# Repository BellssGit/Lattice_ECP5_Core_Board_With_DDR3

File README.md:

# Lattice_ECP5_Core_Board_With_DDR3
A 6 layer Board, Using Lattice LFE5U-25F-BGA256 FPGA with 32bit wide DDR3 memory.

Connectivity:
  
  1. 8 Channel LVDS working up to 800Mbps per channel
  2. 24bit RGB display or general IO
  3. FT232H with FT245 FIFO support

On Board memory:
  
  1. 128Mbit Flash
  2. 2x2Gbit 16x2bit wide DDR3 memory

A [blog post](https://www.emoe.xyz/lattice_ecp5_board/) about this board (Chinese Only)

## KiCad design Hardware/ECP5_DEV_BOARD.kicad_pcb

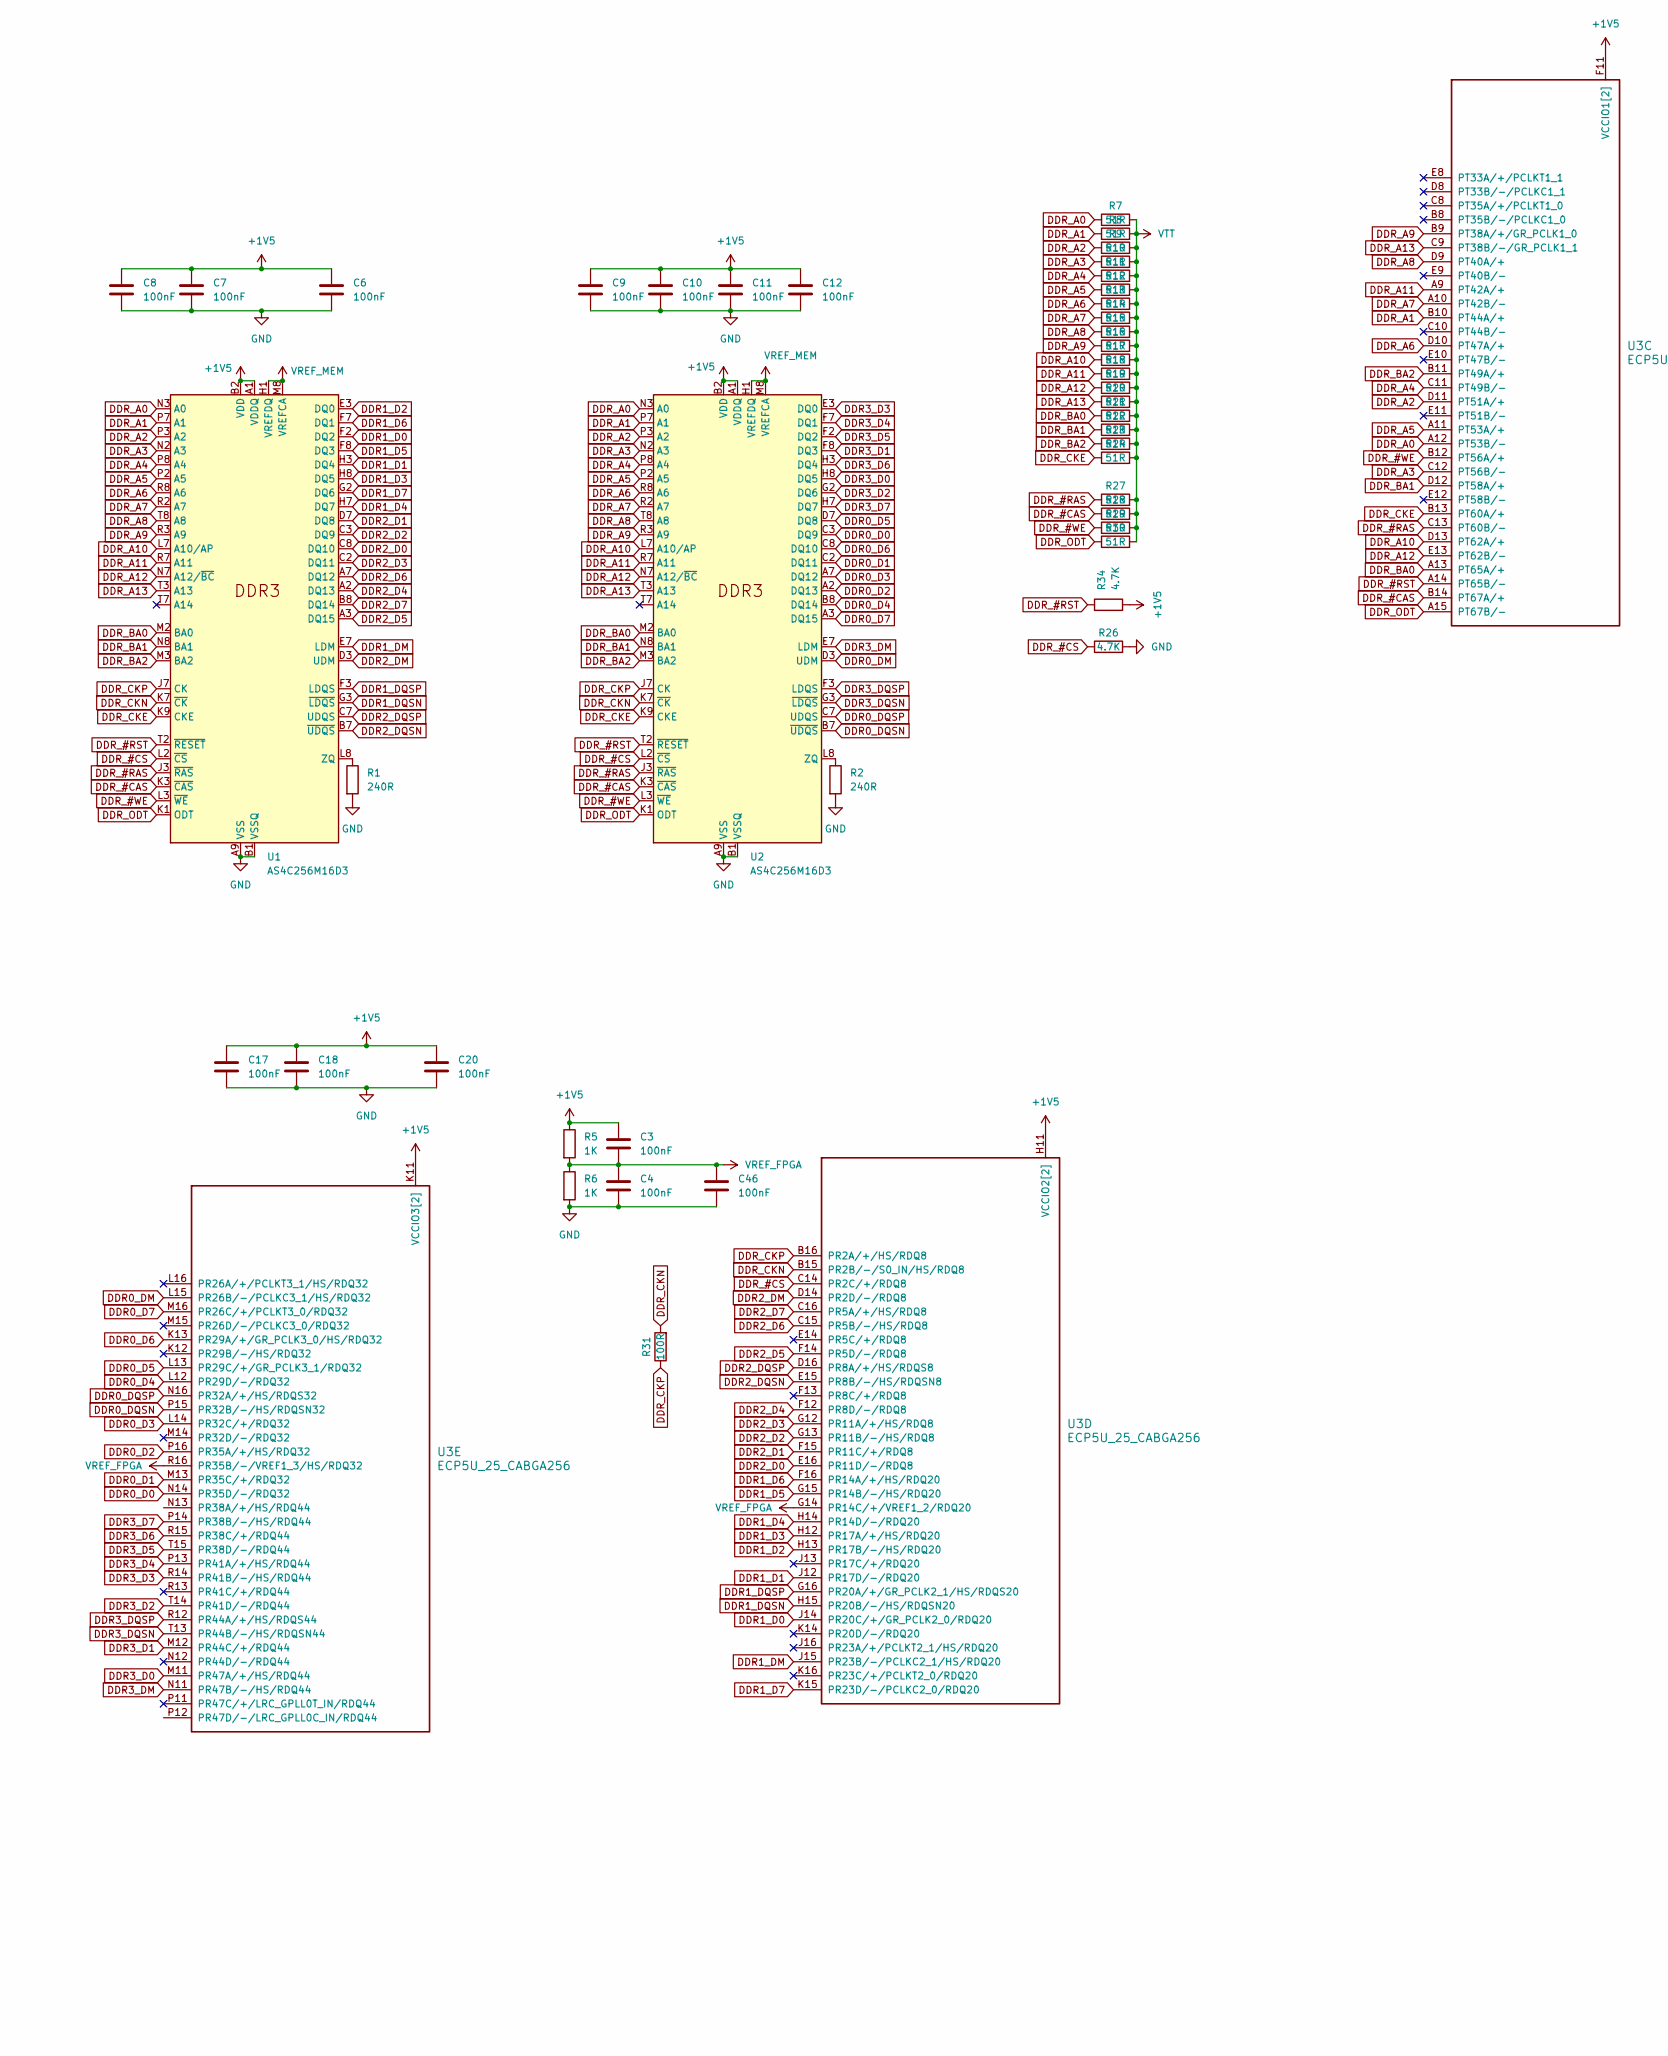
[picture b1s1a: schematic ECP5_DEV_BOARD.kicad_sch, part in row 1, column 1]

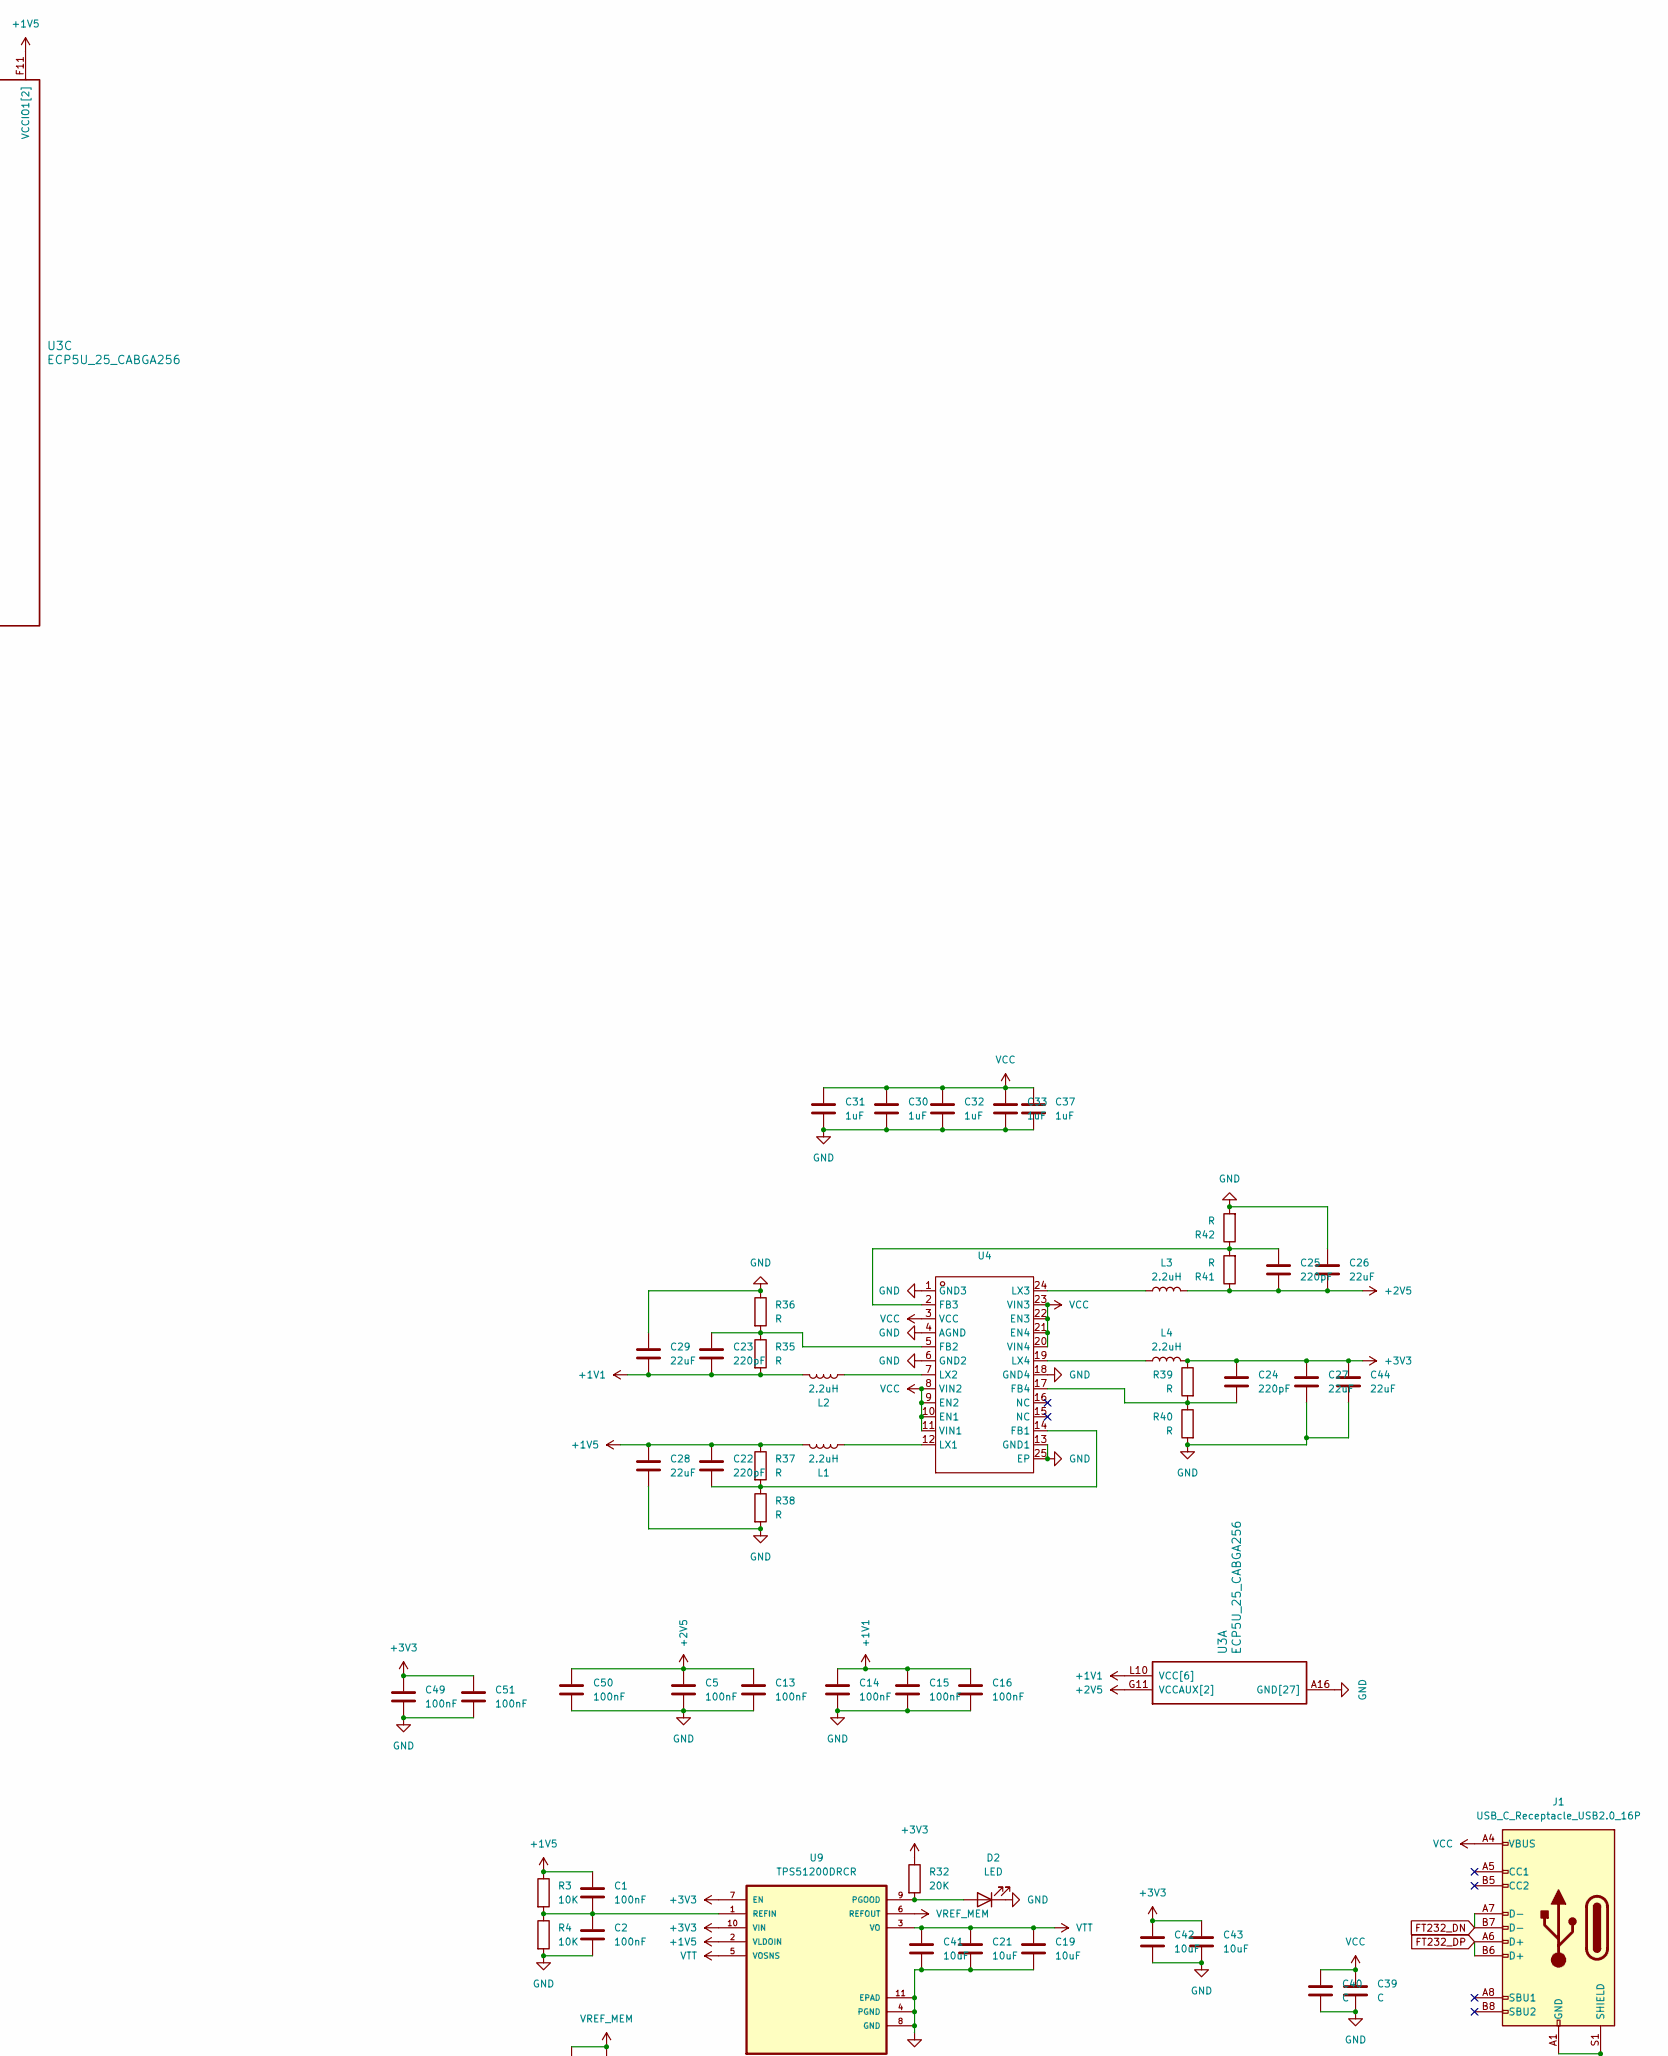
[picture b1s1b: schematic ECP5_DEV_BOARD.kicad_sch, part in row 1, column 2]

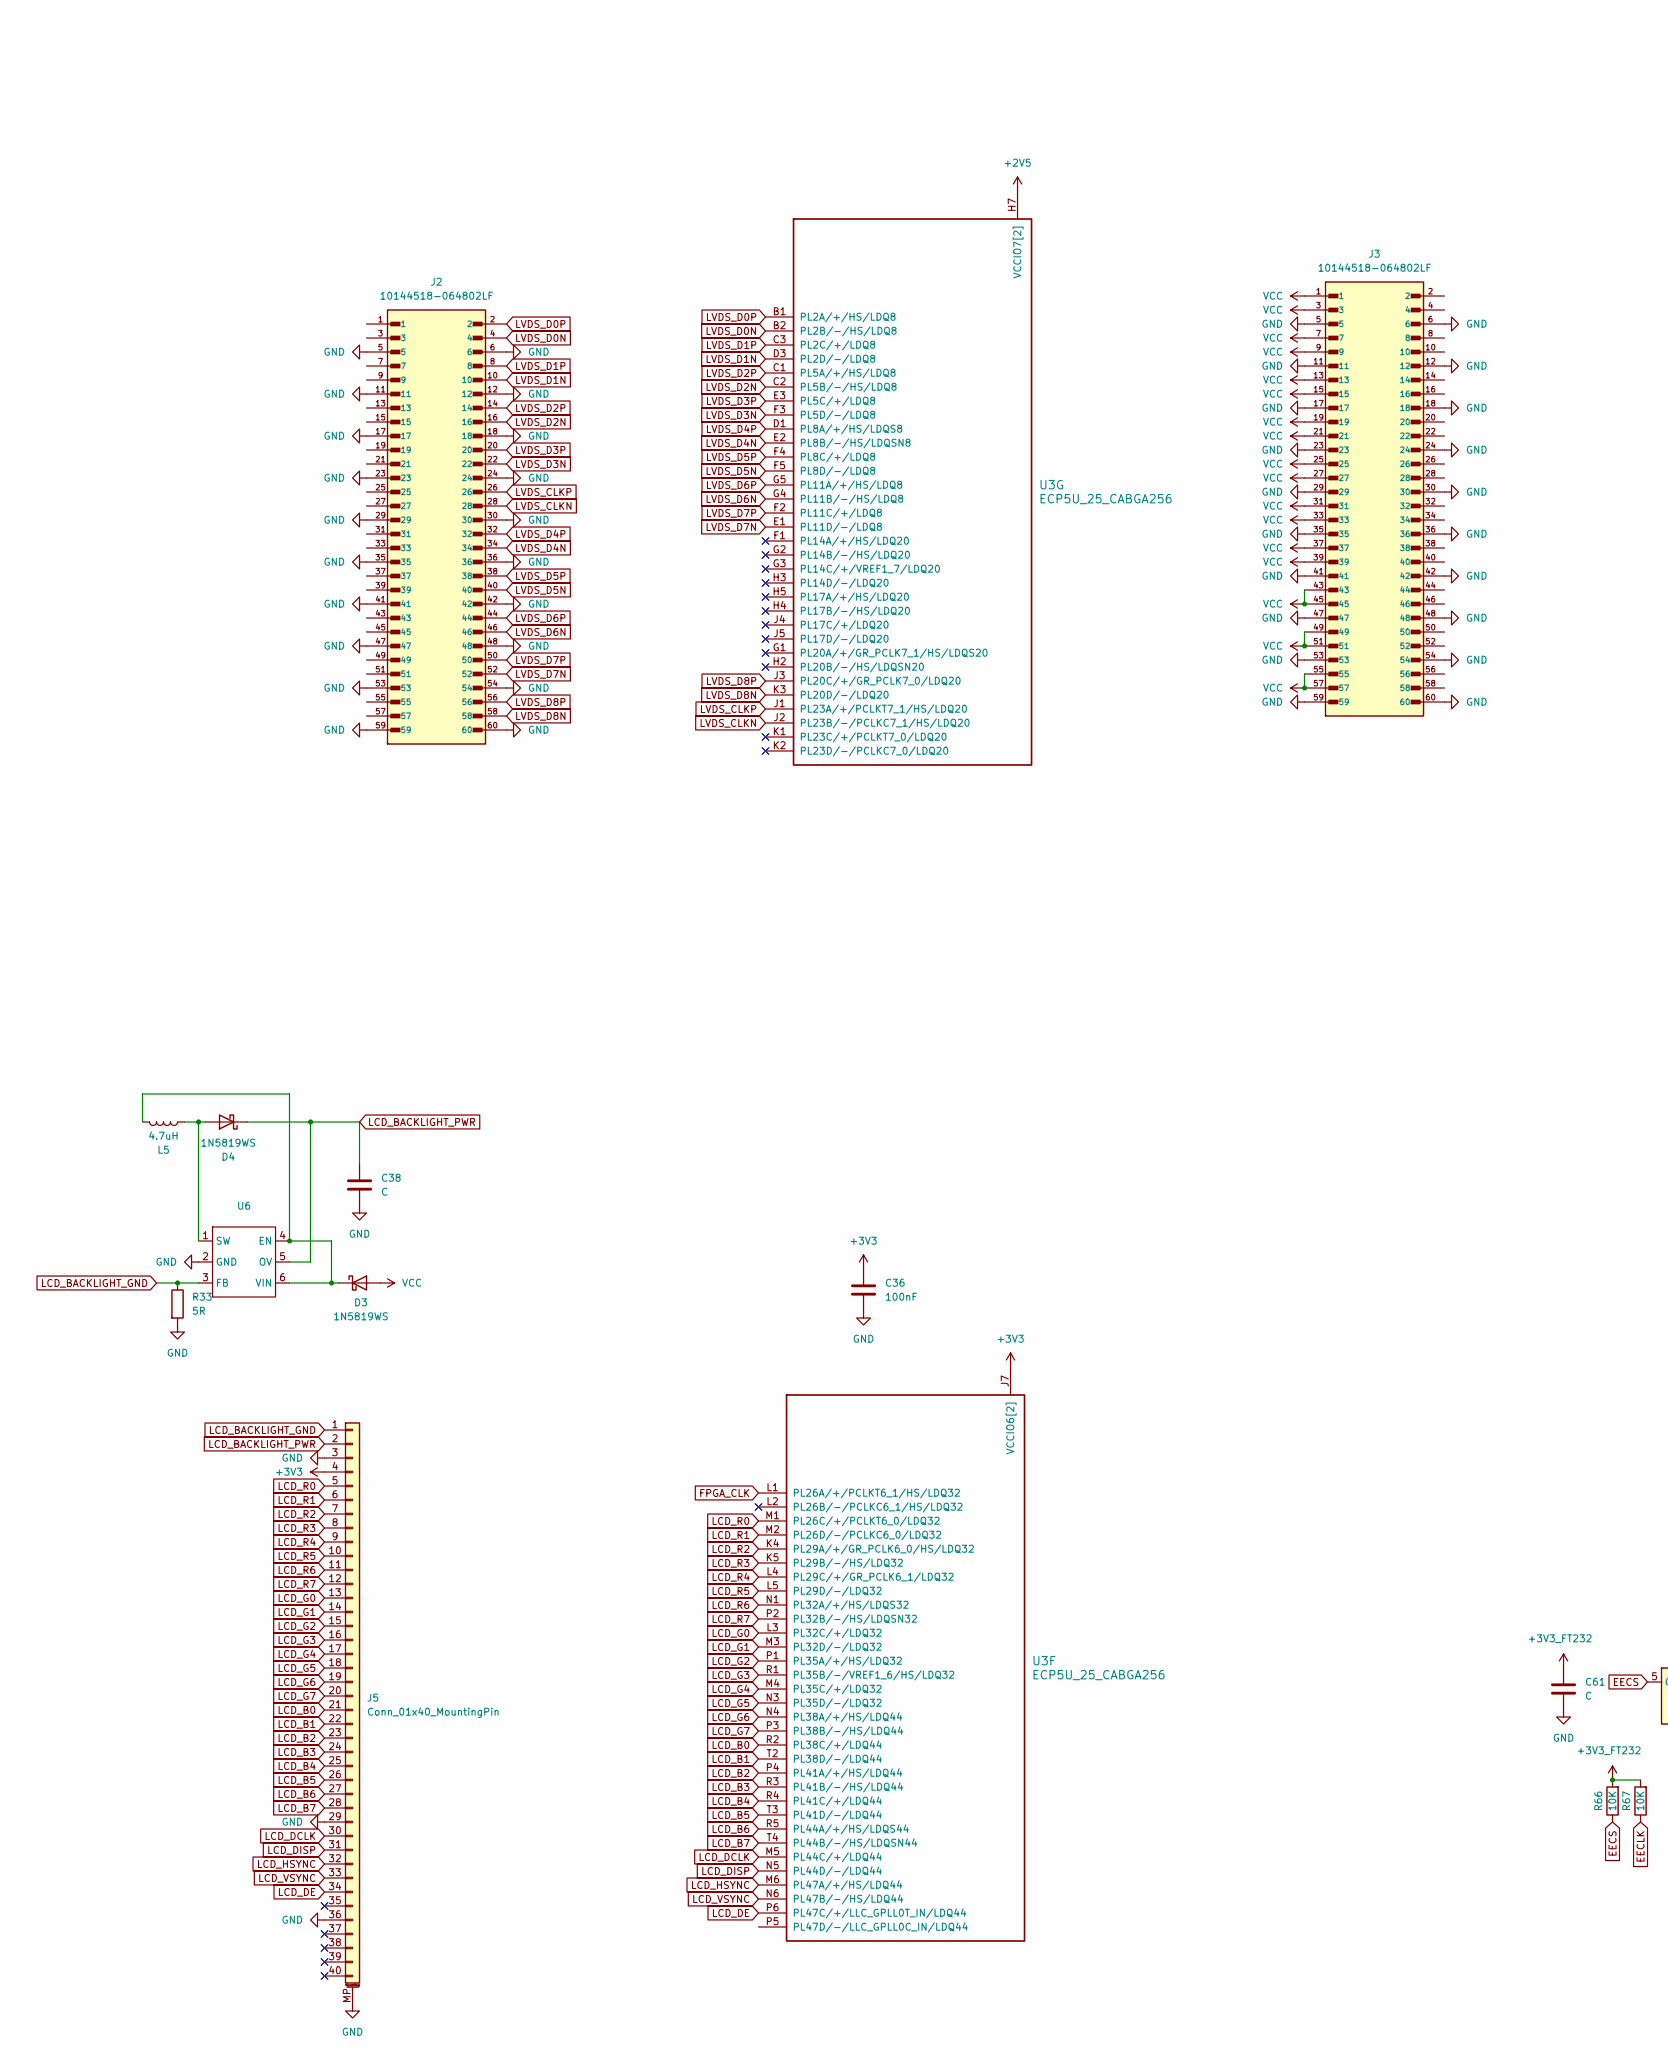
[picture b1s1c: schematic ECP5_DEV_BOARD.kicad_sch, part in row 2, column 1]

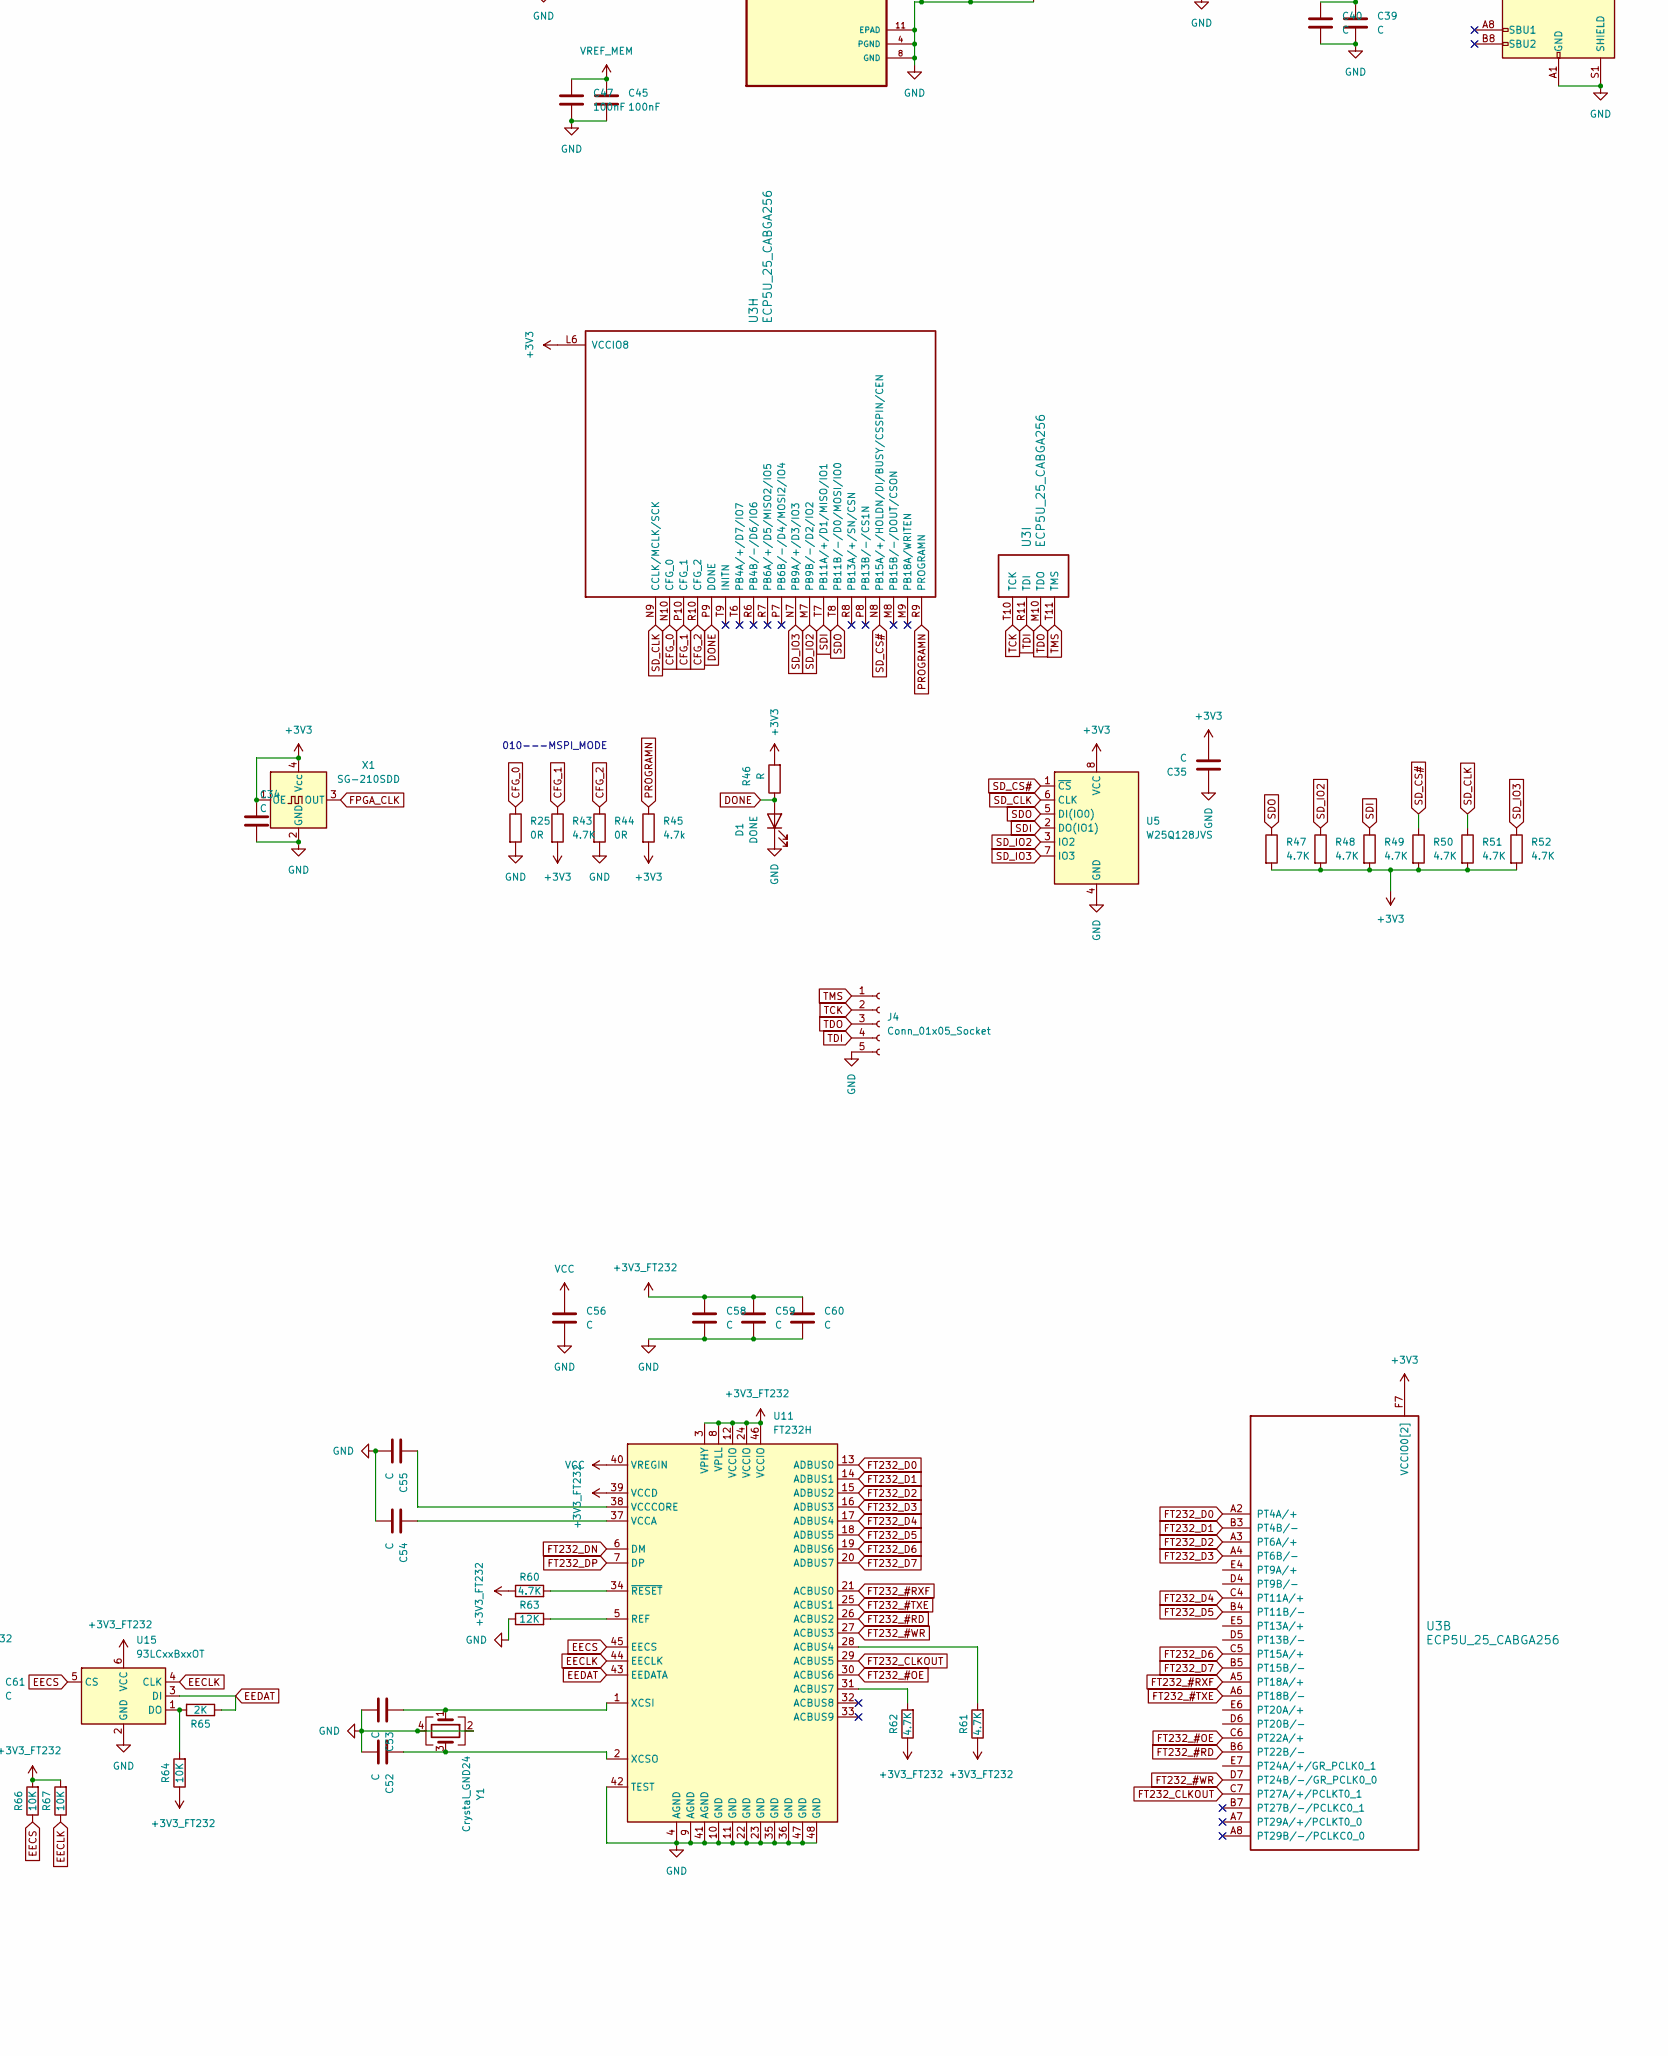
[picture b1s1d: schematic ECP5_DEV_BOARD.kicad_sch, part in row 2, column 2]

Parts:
C1, C2, C3, C4, C47: 100nF; C_0603_1608Metric
C5, C6, C7, C8, C9, C10, C11, C12, C13, C14, C15, C16, C17, C18, C20, C36, C45, C46, C49, C50, C51: 100nF; C_0402_1005Metric
C19, C21, C41, C42, C43: 10uF; C_0603_1608Metric
C22, C23, C24, C25: 220pF; C_0603_1608Metric
C26, C27, C28, C29, C44: 22uF; C_0805_2012Metric
C30, C31, C32, C33, C37: 1uF; C_0603_1608Metric
C34, C35, C52, C53, C54, C55, C56, C58, C59, C60, C61: C; C_0603_1608Metric
C38, C39, C40: C; C_0805_2012Metric
D1: DONE; LED_0603_1608Metric_Pad1.05x0.95mm_HandSolder
D2: LED; LED_0603_1608Metric
D3, D4: 1N5819WS; D_SOD-323
J1: USB_C_Receptacle_USB2.0_16P; USB_C_Receptacle_G-Switch_GT-USB-7010ASV
J2, J3: 10144518-064802LF; AMPHENOL_10144518-064802LF; PARTREV H
J4: Conn_01x05_Socket; PinSocket_1x05_P2.54mm_Vertical
J5: Conn_01x40_MountingPin; TE_4-1734839-0_1x40-1MP_P0.5mm_Horizontal
L1, L2, L3, L4: 2.2uH; L_Changjiang_FNR252010S
L5: 4.7uH; L_Changjiang_FNR252010S
R1, R2: 240R; R_0402_1005Metric
R3, R4, R64, R66, R67: 10K; R_0603_1608Metric
R5, R6: 1K; R_0603_1608Metric
R7, R8, R9, R10, R11, R12, R13, R14, R15, R16, R17, R18, R19, R20, R21, R22, R23, R24, R27, R28, R29, R30: 51R; R_0402_1005Metric
R25, R44: 0R; R_0402_1005Metric
R26, R34, R43: 4.7K; R_0402_1005Metric
R31: 100R; R_0402_1005Metric
R32: 20K; R_0603_1608Metric
R33: 5R; R_0603_1608Metric
R35, R36, R37, R38, R39, R40, R41, R42: R; R_0603_1608Metric
R45: 4.7k; R_0402_1005Metric
R46: R; R_0603_1608Metric_Pad0.98x0.95mm_HandSolder
R47, R48, R49, R50, R51, R52: 4.7K; R_0603_1608Metric_Pad0.98x0.95mm_HandSolder
R60, R61, R62: 4.7K; R_0603_1608Metric
R63: 12K; R_0603_1608Metric
R65: 2K; R_0603_1608Metric
U1, U2: AS4C256M16D3; BGA-96_9.0x13.0mm_Layout2x3x16_P0.8mm
U3: ECP5U_25_CABGA256; BGA-256_14.0x14.0mm_Layout16x16_P0.8mm_Ball0.45mm_Pad0.32mm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
U4: VQFN-24-1EP_4x4mm_P0.5mm_EP2.5x2.5mm
U5: W25Q128JVS; SOIC-8_5.23x5.23mm_P1.27mm
U6: SOT-23-6
U9: TPS51200DRCR; VREG_V62_16624-01YE
U11: FT232H; LQFP-48_7x7mm_P0.5mm
U15: 93LCxxBxxOT; SOT-23-6
X1: SG-210SDD; Oscillator_SMD_Abracon_ASE-4Pin_3.2x2.5mm
Y1: Crystal_GND24; Crystal_SMD_3225-4Pin_3.2x2.5mm

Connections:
+1V1: C14.1, C15.1, C16.1, C23.2, C29.2, L2.1, R35.2, U3.G6 (VCC[6]), U3.G7 (VCC[6]), U3.G9 (VCC[6]), U3.L8 (VCC[6]), U3.L9 (VCC[6]), U3.L10 (VCC[6])
+1V5: C1.1, C3.1, C6.1, C7.1, C8.1, C9.1, C10.1, C11.1, C12.1, C17.1, C18.1, C20.1, C22.1, C28.1, L1.1, R3.1, R5.1, R34.2, R37.1, U1.A1 (VDDQ), U1.A8 (VDDQ), U1.B2 (VDD), U1.C1 (VDDQ), U1.C9 (VDDQ), U1.D2 (VDDQ), U1.D9 (VDD), U1.E9 (VDDQ), U1.F1 (VDDQ), U1.G7 (VDD), U1.H2 (VDDQ), U1.H9 (VDDQ), U1.K2 (VDD), U1.K8 (VDD), U1.N1 (VDD), U1.N9 (VDD), U1.R1 (VDD), U1.R9 (VDD), U2.A1 (VDDQ), U2.A8 (VDDQ), U2.B2 (VDD), U2.C1 (VDDQ), U2.C9 (VDDQ), U2.D2 (VDDQ), U2.D9 (VDD), U2.E9 (VDDQ), U2.F1 (VDDQ), U2.G7 (VDD), U2.H2 (VDDQ), U2.H9 (VDDQ), U2.K2 (VDD), U2.K8 (VDD), U2.N1 (VDD), U2.N9 (VDD), U2.R1 (VDD), U2.R9 (VDD), U3.F10 (VCCIO1[2]), U3.F11 (VCCIO1[2]), U3.H11 (VCCIO2[2]), U3.J11 (VCCIO2[2]), U3.K11 (VCCIO3[2]), U3.L11 (VCCIO3[2]), U9.2 (VLDOIN)
+2V5: C5.1, C13.1, C25.1, C26.2, C50.1, L3.2, R41.1, U3.G11 (VCCAUX[2]), U3.H6 (VCCIO7[2]), U3.H7 (VCCIO7[2]), U3.L7 (VCCAUX[2])
+3V3: C24.1, C27.1, C34.1, C35.2, C36.1, C42.1, C43.1, C44.1, C49.1, C51.1, J5.4, L4.2, R32.1, R39.1, R43.2, R45.2, R46.2, R47.2, R48.2, R49.2, R50.2, R51.2, R52.2, U3.F6 (VCCIO0[2]), U3.F7 (VCCIO0[2]), U3.J6 (VCCIO6[2]), U3.J7 (VCCIO6[2]), U3.L6 (VCCIO8), U5.8 (VCC), U9.7 (EN), U9.10 (VIN), X1.1 (OE), X1.4 (Vcc)
+3V3_FT232: C58.1, C59.1, C60.1, C61.1, R60.1, R61.1, R62.1, R64.1, R66.2, R67.2, U11.3 (VPHY), U11.8 (VPLL), U11.12 (VCCIO), U11.24 (VCCIO), U11.39 (VCCD), U11.46 (VCCIO), U15.6 (VCC)
CFG_0: R25.1, U3.N10 (CFG_0)
CFG_1: R43.1, U3.P10 (CFG_1)
CFG_2: R44.1, U3.R10 (CFG_2)
DDR0_D0: U2.C3 (DQ9), U3.N14 (PR35D/-/RDQ32)
DDR0_D1: U2.C2 (DQ11), U3.M13 (PR35C/+/RDQ32)
DDR0_D2: U2.A2 (DQ13), U3.P16 (PR35A/+/HS/RDQ32)
DDR0_D3: U2.A7 (DQ12), U3.L14 (PR32C/+/RDQ32)
DDR0_D4: U2.B8 (DQ14), U3.L12 (PR29D/-/RDQ32)
DDR0_D5: U2.D7 (DQ8), U3.L13 (PR29C/+/GR_PCLK3_1/RDQ32)
DDR0_D6: U2.C8 (DQ10), U3.K13 (PR29A/+/GR_PCLK3_0/HS/RDQ32)
DDR0_D7: U2.A3 (DQ15), U3.M16 (PR26C/+/PCLKT3_0/RDQ32)
DDR0_DM: U2.D3 (UDM), U3.L15 (PR26B/-/PCLKC3_1/HS/RDQ32)
DDR0_DQSN: U2.B7 (~UDQS), U3.P15 (PR32B/-/HS/RDQSN32)
DDR0_DQSP: U2.C7 (UDQS), U3.N16 (PR32A/+/HS/RDQS32)
DDR1_D0: U1.F2 (DQ2), U3.J14 (PR20C/+/GR_PCLK2_0/RDQ20)
DDR1_D1: U1.H3 (DQ4), U3.J12 (PR17D/-/RDQ20)
DDR1_D2: U1.E3 (DQ0), U3.H13 (PR17B/-/HS/RDQ20)
DDR1_D3: U1.H8 (DQ5), U3.H12 (PR17A/+/HS/RDQ20)
DDR1_D4: U1.H7 (DQ7), U3.H14 (PR14D/-/RDQ20)
DDR1_D5: U1.F8 (DQ3), U3.G15 (PR14B/-/HS/RDQ20)
DDR1_D6: U1.F7 (DQ1), U3.F16 (PR14A/+/HS/RDQ20)
DDR1_D7: U1.G2 (DQ6), U3.K15 (PR23D/-/PCLKC2_0/RDQ20)
DDR1_DM: U1.E7 (LDM), U3.J15 (PR23B/-/PCLKC2_1/HS/RDQ20)
DDR1_DQSN: U1.G3 (~LDQS), U3.H15 (PR20B/-/HS/RDQSN20)
DDR1_DQSP: U1.F3 (LDQS), U3.G16 (PR20A/+/GR_PCLK2_1/HS/RDQS20)
DDR2_D0: U1.C8 (DQ10), U3.E16 (PR11D/-/RDQ8)
DDR2_D1: U1.D7 (DQ8), U3.F15 (PR11C/+/RDQ8)
DDR2_D2: U1.C3 (DQ9), U3.G13 (PR11B/-/HS/RDQ8)
DDR2_D3: U1.C2 (DQ11), U3.G12 (PR11A/+/HS/RDQ8)
DDR2_D4: U1.A2 (DQ13), U3.F12 (PR8D/-/RDQ8)
DDR2_D5: U1.A3 (DQ15), U3.F14 (PR5D/-/RDQ8)
DDR2_D6: U1.A7 (DQ12), U3.C15 (PR5B/-/HS/RDQ8)
DDR2_D7: U1.B8 (DQ14), U3.C16 (PR5A/+/HS/RDQ8)
DDR2_DM: U1.D3 (UDM), U3.D14 (PR2D/-/RDQ8)
DDR2_DQSN: U1.B7 (~UDQS), U3.E15 (PR8B/-/HS/RDQSN8)
DDR2_DQSP: U1.C7 (UDQS), U3.D16 (PR8A/+/HS/RDQS8)
DDR3_D0: U2.H8 (DQ5), U3.M11 (PR47A/+/HS/RDQ44)
DDR3_D1: U2.F8 (DQ3), U3.M12 (PR44C/+/RDQ44)
DDR3_D2: U2.G2 (DQ6), U3.T14 (PR41D/-/RDQ44)
DDR3_D3: U2.E3 (DQ0), U3.R14 (PR41B/-/HS/RDQ44)
DDR3_D4: U2.F7 (DQ1), U3.P13 (PR41A/+/HS/RDQ44)
DDR3_D5: U2.F2 (DQ2), U3.T15 (PR38D/-/RDQ44)
DDR3_D6: U2.H3 (DQ4), U3.R15 (PR38C/+/RDQ44)
DDR3_D7: U2.H7 (DQ7), U3.P14 (PR38B/-/HS/RDQ44)
DDR3_DM: U2.E7 (LDM), U3.N11 (PR47B/-/HS/RDQ44)
DDR3_DQSN: U2.G3 (~LDQS), U3.T13 (PR44B/-/HS/RDQSN44)
DDR3_DQSP: U2.F3 (LDQS), U3.R12 (PR44A/+/HS/RDQS44)
DDR_#CAS: R28.1, U1.K3 (~CAS), U2.K3 (~CAS), U3.B14 (PT67A/+)
DDR_#CS: R26.1, U1.L2 (~CS), U2.L2 (~CS), U3.C14 (PR2C/+/RDQ8)
DDR_#RAS: R27.1, U1.J3 (~RAS), U2.J3 (~RAS), U3.C13 (PT60B/-)
DDR_#RST: R34.1, U1.T2 (~RESET), U2.T2 (~RESET), U3.A14 (PT65B/-)
DDR_#WE: R29.1, U1.L3 (~WE), U2.L3 (~WE), U3.B12 (PT56A/+)
DDR_A0: R7.1, U1.N3 (A0), U2.N3 (A0), U3.A12 (PT53B/-)
DDR_A1: R8.1, U1.P7 (A1), U2.P7 (A1), U3.B10 (PT44A/+)
DDR_A2: R9.1, U1.P3 (A2), U2.P3 (A2), U3.D11 (PT51A/+)
DDR_A3: R10.1, U1.N2 (A3), U2.N2 (A3), U3.C12 (PT56B/-)
DDR_A4: R11.1, U1.P8 (A4), U2.P8 (A4), U3.C11 (PT49B/-)
DDR_A5: R12.1, U1.P2 (A5), U2.P2 (A5), U3.A11 (PT53A/+)
DDR_A6: R13.1, U1.R8 (A6), U2.R8 (A6), U3.D10 (PT47A/+)
DDR_A7: R14.1, U1.R2 (A7), U2.R2 (A7), U3.A10 (PT42B/-)
DDR_A8: R15.1, U1.T8 (A8), U2.T8 (A8), U3.D9 (PT40A/+)
DDR_A9: R16.1, U1.R3 (A9), U2.R3 (A9), U3.B9 (PT38A/+/GR_PCLK1_0)
DDR_A10: R17.1, U1.L7 (A10/AP), U2.L7 (A10/AP), U3.D13 (PT62A/+)
DDR_A11: R18.1, U1.R7 (A11), U2.R7 (A11), U3.A9 (PT42A/+)
DDR_A12: R19.1, U1.N7 (A12/~BC), U2.N7 (A12/~BC), U3.E13 (PT62B/-)
DDR_A13: R20.1, U1.T3 (A13), U2.T3 (A13), U3.C9 (PT38B/-/GR_PCLK1_1)
DDR_BA0: R21.1, U1.M2 (BA0), U2.M2 (BA0), U3.A13 (PT65A/+)
DDR_BA1: R22.1, U1.N8 (BA1), U2.N8 (BA1), U3.D12 (PT58A/+)
DDR_BA2: R23.1, U1.M3 (BA2), U2.M3 (BA2), U3.B11 (PT49A/+)
DDR_CKE: R24.1, U1.K9 (CKE), U2.K9 (CKE), U3.B13 (PT60A/+)
DDR_CKN: R31.2, U1.K7 (~CK), U2.K7 (~CK), U3.B15 (PR2B/-/S0_IN/HS/RDQ8)
DDR_CKP: R31.1, U1.J7 (CK), U2.J7 (CK), U3.B16 (PR2A/+/HS/RDQ8)
DDR_ODT: R30.1, U1.K1 (ODT), U2.K1 (ODT), U3.A15 (PT67B/-)
DONE: D1.2 (A), R46.1, U3.P9 (DONE)
EECLK: R67.1, U11.44 (EECLK), U15.4 (CLK)
EECS: R66.1, U11.45 (EECS), U15.5 (CS)
EEDAT: R65.1, U11.43 (EEDATA), U15.3 (DI)
FPGA_CLK: U3.L1 (PL26A/+/PCLKT6_1/HS/LDQ32), X1.3 (OUT)
FT232_#OE: U3.C6 (PT22A/+), U11.30 (ACBUS6)
FT232_#RD: U3.B6 (PT22B/-), U11.26 (ACBUS2)
FT232_#RXF: U3.A5 (PT18A/+), U11.21 (ACBUS0)
FT232_#TXE: U3.A6 (PT18B/-), U11.25 (ACBUS1)
FT232_#WR: U3.D7 (PT24B/-/GR_PCLK0_0), U11.27 (ACBUS3)
FT232_CLKOUT: U3.C7 (PT27A/+/PCLKT0_1), U11.29 (ACBUS5)
FT232_D0: U3.A2 (PT4A/+), U11.13 (ADBUS0)
FT232_D1: U3.B3 (PT4B/-), U11.14 (ADBUS1)
FT232_D2: U3.A3 (PT6A/+), U11.15 (ADBUS2)
FT232_D3: U3.A4 (PT6B/-), U11.16 (ADBUS3)
FT232_D4: U3.C4 (PT11A/+), U11.17 (ADBUS4)
FT232_D5: U3.B4 (PT11B/-), U11.18 (ADBUS5)
FT232_D6: U3.C5 (PT15A/+), U11.19 (ADBUS6)
FT232_D7: U3.B5 (PT15B/-), U11.20 (ADBUS7)
FT232_DN: J1.A7 (D-), J1.B7 (D-), U11.6 (DM)
FT232_DP: J1.A6 (D+), J1.B6 (D+), U11.7 (DP)
GND: C2.2, C4.2, C5.2, C6.2, C7.2, C8.2, C9.2, C10.2, C11.2, C12.2, C13.2, C14.2, C15.2, C16.2, C17.2, C18.2, C19.2, C20.2, C21.2, C26.1, C27.2, C28.2, C29.1, C30.1, C31.1, C32.1, C33.1, C34.2, C35.1, C36.2, C37.1, C38.2, C39.2, C40.2, C41.2, C42.2, C43.2, C44.2, C45.2, C46.2, C47.2, C49.2, C50.2, C51.2, C52.2, C53.2, C54.2, C55.2, C56.2, C58.2, C59.2, C60.2, C61.2, D1.1 (K), D2.1 (K), J1.A1 (GND), J1.A12 (GND), J1.B1 (GND), J1.B12 (GND), J1.S1 (SHIELD), J2.5, J2.6, J2.11, J2.12, J2.17, J2.18, J2.23, J2.24, J2.29, J2.30, J2.35, J2.36, J2.41, J2.42, J2.47, J2.48, J2.53, J2.54, J2.59, J2.60, J3.5, J3.6, J3.11, J3.12, J3.17, J3.18, J3.23, J3.24, J3.29, J3.30, J3.35, J3.36, J3.41, J3.42, J3.47, J3.48, J3.53, J3.54, J3.59, J3.60, J4.5, J5.3, J5.29, J5.36, J5.MP (MountPin), R1.2, R2.2, R4.2, R6.2, R25.2, R26.2, R33.2, R36.1, R38.2, R40.2, R42.2, R44.2, R63.1, U1.A9 (VSS), U1.B1 (VSSQ), U1.B3 (VSS), U1.B9 (VSSQ), U1.D1 (VSSQ), U1.D8 (VSSQ), U1.E1 (VSS), U1.E2 (VSSQ), U1.E8 (VSSQ), U1.F9 (VSSQ), U1.G1 (VSSQ), U1.G8 (VSS), U1.G9 (VSSQ), U1.J2 (VSS), U1.J8 (VSS), U1.M1 (VSS), U1.M9 (VSS), U1.P1 (VSS), U1.P9 (VSS), U1.T1 (VSS), U1.T9 (VSS), U2.A9 (VSS), U2.B1 (VSSQ), U2.B3 (VSS), U2.B9 (VSSQ), U2.D1 (VSSQ), U2.D8 (VSSQ), U2.E1 (VSS), U2.E2 (VSSQ), U2.E8 (VSSQ), U2.F9 (VSSQ), U2.G1 (VSSQ), U2.G8 (VSS), U2.G9 (VSSQ), U2.J2 (VSS), U2.J8 (VSS), U2.M1 (VSS), U2.M9 (VSS), U2.P1 (VSS), U2.P9 (VSS), U2.T1 (VSS), U2.T9 (VSS), U3.A1 (GND[27]), U3.A16 (GND[27]), U3.D2 (GND[27]), U3.D15 (GND[27]), U3.F8 (GND[27]), U3.F9 (GND[27]), U3.G8 (GND[27]), U3.G10 (GND[27]), U3.H1 (GND[27]), U3.H8 (GND[27]), U3.H9 (GND[27]), U3.H10 (GND[27]), U3.H16 (GND[27]), U3.J8 (GND[27]), U3.J9 (GND[27]), U3.J10 (GND[27]), U3.K6 (GND[27]), U3.K7 (GND[27]), U3.K8 (GND[27]), U3.K9 (GND[27]), U3.K10 (GND[27]), U3.N2 (GND[27]), U3.N15 (GND[27]), U3.T1 (GND[27]), U3.T5 (GND[27]), U3.T12 (GND[27]), U3.T16 (GND[27]), U4.1 (GND3), U4.4 (AGND), U4.6 (GND2), U4.13 (GND1), U4.18 (GND4), U4.25 (EP), U5.4 (GND), U6.2 (GND), U9.4 (PGND), U9.8 (GND), U9.11 (EPAD), U11.4 (AGND), U11.9 (AGND), U11.10 (GND), U11.11 (GND), U11.22 (GND), U11.23 (GND), U11.35 (GND), U11.36 (GND), U11.41 (AGND), U11.42 (TEST), U11.47 (GND), U11.48 (GND), U15.2 (GND), X1.2 (GND), Y1.2, Y1.4
LCD_B0: J5.21, U3.R2 (PL38C/+/LDQ44)
LCD_B1: J5.22, U3.T2 (PL38D/-/LDQ44)
LCD_B2: J5.23, U3.P4 (PL41A/+/HS/LDQ44)
LCD_B3: J5.24, U3.R3 (PL41B/-/HS/LDQ44)
LCD_B4: J5.25, U3.R4 (PL41C/+/LDQ44)
LCD_B5: J5.26, U3.T3 (PL41D/-/LDQ44)
LCD_B6: J5.27, U3.R5 (PL44A/+/HS/LDQS44)
LCD_B7: J5.28, U3.T4 (PL44B/-/HS/LDQSN44)
LCD_BACKLIGHT_GND: J5.1, R33.1, U6.3 (FB)
LCD_BACKLIGHT_PWR: C38.1, D4.1 (K), J5.2, U6.5 (OV)
LCD_DCLK: J5.30, U3.M5 (PL44C/+/LDQ44)
LCD_DE: J5.34, U3.P6 (PL47C/+/LLC_GPLL0T_IN/LDQ44)
LCD_DISP: J5.31, U3.N5 (PL44D/-/LDQ44)
LCD_G0: J5.13, U3.L3 (PL32C/+/LDQ32)
LCD_G1: J5.14, U3.M3 (PL32D/-/LDQ32)
LCD_G2: J5.15, U3.P1 (PL35A/+/HS/LDQ32)
LCD_G3: J5.16, U3.R1 (PL35B/-/VREF1_6/HS/LDQ32)
LCD_G4: J5.17, U3.M4 (PL35C/+/LDQ32)
LCD_G5: J5.18, U3.N3 (PL35D/-/LDQ32)
LCD_G6: J5.19, U3.N4 (PL38A/+/HS/LDQ44)
LCD_G7: J5.20, U3.P3 (PL38B/-/HS/LDQ44)
LCD_HSYNC: J5.32, U3.M6 (PL47A/+/HS/LDQ44)
LCD_R0: J5.5, U3.M1 (PL26C/+/PCLKT6_0/LDQ32)
LCD_R1: J5.6, U3.M2 (PL26D/-/PCLKC6_0/LDQ32)
LCD_R2: J5.7, U3.K4 (PL29A/+/GR_PCLK6_0/HS/LDQ32)
LCD_R3: J5.8, U3.K5 (PL29B/-/HS/LDQ32)
LCD_R4: J5.9, U3.L4 (PL29C/+/GR_PCLK6_1/LDQ32)
LCD_R5: J5.10, U3.L5 (PL29D/-/LDQ32)
LCD_R6: J5.11, U3.N1 (PL32A/+/HS/LDQS32)
LCD_R7: J5.12, U3.P2 (PL32B/-/HS/LDQSN32)
LCD_VSYNC: J5.33, U3.N6 (PL47B/-/HS/LDQ44)
LVDS_CLKN: J2.28, U3.J2 (PL23B/-/PCLKC7_1/HS/LDQ20)
LVDS_CLKP: J2.26, U3.J1 (PL23A/+/PCLKT7_1/HS/LDQ20)
LVDS_D0N: J2.4, U3.B2 (PL2B/-/HS/LDQ8)
LVDS_D0P: J2.2, U3.B1 (PL2A/+/HS/LDQ8)
LVDS_D1N: J2.10, U3.D3 (PL2D/-/LDQ8)
LVDS_D1P: J2.8, U3.C3 (PL2C/+/LDQ8)
LVDS_D2N: J2.16, U3.C2 (PL5B/-/HS/LDQ8)
LVDS_D2P: J2.14, U3.C1 (PL5A/+/HS/LDQ8)
LVDS_D3N: J2.22, U3.F3 (PL5D/-/LDQ8)
LVDS_D3P: J2.20, U3.E3 (PL5C/+/LDQ8)
LVDS_D4N: J2.34, U3.E2 (PL8B/-/HS/LDQSN8)
LVDS_D4P: J2.32, U3.D1 (PL8A/+/HS/LDQS8)
LVDS_D5N: J2.40, U3.F5 (PL8D/-/LDQ8)
LVDS_D5P: J2.38, U3.F4 (PL8C/+/LDQ8)
LVDS_D6N: J2.46, U3.G4 (PL11B/-/HS/LDQ8)
LVDS_D6P: J2.44, U3.G5 (PL11A/+/HS/LDQ8)
LVDS_D7N: J2.52, U3.E1 (PL11D/-/LDQ8)
LVDS_D7P: J2.50, U3.F2 (PL11C/+/LDQ8)
LVDS_D8N: J2.58, U3.K3 (PL20D/-/LDQ20)
LVDS_D8P: J2.56, U3.J3 (PL20C/+/GR_PCLK7_0/LDQ20)
unnamed: D2.2 (A), R32.2, U9.9 (PGOOD)
unnamed: D3.1 (K), L5.2, U6.4 (EN), U6.6 (VIN)
unnamed: D4.2 (A), L5.1, U6.1 (SW)
unnamed: R1.1, U1.L8 (ZQ)
unnamed: R2.1, U2.L8 (ZQ)
unnamed: C22.2, R37.2, R38.1, U4.14 (FB1)
unnamed: C23.1, R35.1, R36.2, U4.5 (FB2)
unnamed: C25.2, R41.2, R42.1, U4.2 (FB3)
unnamed: C24.2, R39.2, R40.1, U4.17 (FB4)
unnamed: L1.2, U4.12 (LX1)
unnamed: L2.2, U4.7 (LX2)
unnamed: L3.1, U4.24 (LX3)
unnamed: L4.1, U4.19 (LX4)
unnamed: C1.2, C2.1, R3.2, R4.1, U9.1 (REFIN)
unnamed: R61.2, U11.28 (ACBUS4)
unnamed: R62.2, U11.31 (ACBUS7)
unnamed: R63.2, U11.5 (REF)
unnamed: C54.1, U11.37 (VCCA)
unnamed: C55.1, U11.38 (VCCCORE)
unnamed: C53.1, U11.1 (XCSI), Y1.1
unnamed: C52.1, U11.2 (XCSO), Y1.3
unnamed: R60.2, U11.34 (~RESET)
unnamed: R64.2, R65.2, U15.1 (DO)
PROGRAMN: R45.1, U3.R9 (PROGRAMN)
SDI: R49.1, U3.T7 (PB11A/+/D1/MISO/IO1), U5.2 (DO(IO1))
SDO: R47.1, U3.T8 (PB11B/-/D0/MOSI/IO0), U5.5 (DI(IO0))
SD_CLK: R51.1, U3.N9 (CCLK/MCLK/SCK), U5.6 (CLK)
SD_CS#: R50.1, U3.N8 (PB15A/+/HOLDN/DI/BUSY/CSSPIN/CEN), U5.1 (~CS)
SD_IO2: R48.1, U3.M7 (PB9B/-/D2/IO2), U5.3 (IO2)
SD_IO3: R52.1, U3.N7 (PB9A/+/D3/IO3), U5.7 (IO3)
TCK: J4.2, U3.T10 (TCK)
TDI: J4.4, U3.R11 (TDI)
TDO: J4.3, U3.M10 (TDO)
TMS: J4.1, U3.T11 (TMS)
VCC: C30.2, C31.2, C32.2, C33.2, C37.2, C39.1, C40.1, C56.1, D3.2 (A), J1.A4 (VBUS), J1.A9 (VBUS), J1.B4 (VBUS), J1.B9 (VBUS), J3.1, J3.3, J3.7, J3.9, J3.13, J3.15, J3.19, J3.21, J3.25, J3.27, J3.31, J3.33, J3.37, J3.39, J3.43, J3.45, J3.49, J3.51, J3.55, J3.57, U4.3 (VCC), U4.8 (VIN2), U4.9 (EN2), U4.10 (EN1), U4.11 (VIN1), U4.20 (VIN4), U4.21 (EN4), U4.22 (EN3), U4.23 (VIN3), U11.40 (VREGIN)
VREF_FPGA: C3.2, C4.1, C46.1, R5.2, R6.1, U3.G14 (PR14C/+/VREF1_2/RDQ20), U3.R16 (PR35B/-/VREF1_3/HS/RDQ32)
VREF_MEM: C45.1, C47.1, U1.H1 (VREFDQ), U1.M8 (VREFCA), U2.H1 (VREFDQ), U2.M8 (VREFCA), U9.6 (REFOUT)
VTT: C19.1, C21.1, C41.1, R7.2, R8.2, R9.2, R10.2, R11.2, R12.2, R13.2, R14.2, R15.2, R16.2, R17.2, R18.2, R19.2, R20.2, R21.2, R22.2, R23.2, R24.2, R27.2, R28.2, R29.2, R30.2, U9.3 (VO), U9.5 (VOSNS)

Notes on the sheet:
010---MSPI_MODE
